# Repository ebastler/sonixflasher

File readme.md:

# sonixflasher

I made a small PCB around [the findings of silicagel777](https://github.com/silicagel777/SN8Flash) on how Sonix microcontrollers are programmed. Further information on how to use this PCB can be found in his repository.

Instead of having ot breadboard the components needed for the Sonix onewire protocol, I included those as well as a CH343 onto a single, tiny PCB with a USB-C port and ESD protection for all in/outputs.

NOTE: This PCB has not yet been tested.

|  |  |
|:---:|:---:|
| Top | Bottom |

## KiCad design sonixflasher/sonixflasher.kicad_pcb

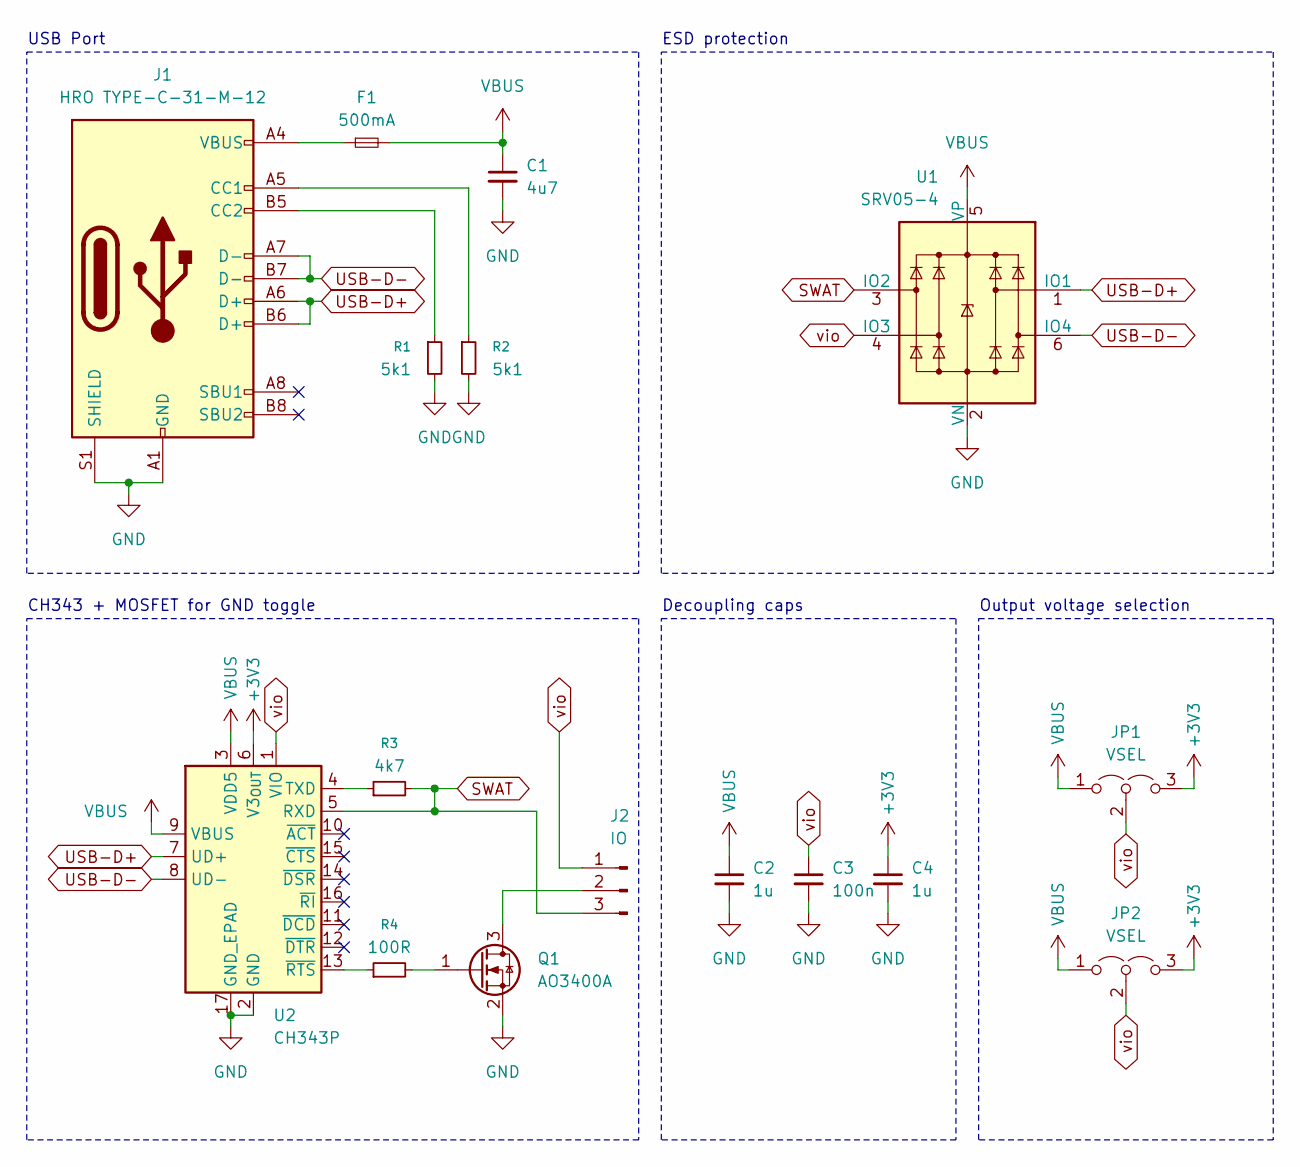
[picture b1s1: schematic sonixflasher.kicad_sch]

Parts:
C1: 4u7; C_0603_1608Metric
C2, C4: 1u; C_0402_1005Metric
C3: 100n; C_0402_1005Metric
F1: 500mA; Fuse_0603_1608Metric
J1: HRO TYPE-C-31-M-12; USB_C_Receptacle_HRO_TYPE-C-31-M-12
J2: IO; PinHeader_1x03_P2.54mm_Horizontal; LCSC C49257
JP1: VSEL; SolderJumper-3_P1.3mm_Open_RoundedPad1.0x1.5mm_NumberLabels
JP2: VSEL; PinHeader_1x03_P2.54mm_Vertical; LCSC C49257
Q1: AO3400A; SOT-23
R1, R2: 5k1; R_0402_1005Metric
R3: 4k7; R_0402_1005Metric
R4: 100R; R_0402_1005Metric
U1: SRV05-4; SOT-23-6-routable
U2: CH343P; WCH_QFN-16-1EP_3x3mm_P0.5mm_EP1.8x1.8mm

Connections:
+3V3: C4.1, JP1.3 (B), JP2.3 (B), U2.6 (V3_{OUT})
GND: C1.2, C2.2, C3.2, C4.2, J1.A1 (GND), J1.A12 (GND), J1.B1 (GND), J1.B12 (GND), J1.S1 (SHIELD), Q1.2 (S), R1.2, R2.2, U1.2 (VN), U2.2 (GND), U2.17 (GND_EPAD)
unnamed: F1.1, J1.A4 (VBUS), J1.A9 (VBUS), J1.B4 (VBUS), J1.B9 (VBUS)
unnamed: J1.A5 (CC1), R2.1
unnamed: J1.B5 (CC2), R1.1
unnamed: J2.2, Q1.3 (D)
unnamed: Q1.1 (G), R4.2
unnamed: R3.1, U2.4 (TXD)
unnamed: R4.1, U2.13 (~RTS)
SWAT: J2.3, R3.2, U1.3 (IO2), U2.5 (RXD)
USB-D+: J1.A6 (D+), J1.B6 (D+), U1.1 (IO1), U2.7 (UD+)
USB-D-: J1.A7 (D-), J1.B7 (D-), U1.6 (IO4), U2.8 (UD-)
VBUS: C1.1, C2.1, F1.2, JP1.1 (A), JP2.1 (A), U1.5 (VP), U2.3 (VDD5), U2.9 (VBUS)
vio: C3.1, J2.1, JP1.2 (C), JP2.2 (C), U1.4 (IO3), U2.1 (VIO)

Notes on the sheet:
Decoupling caps
CH343 + MOSFET for GND toggle
ESD protection
USB Port
Output voltage selection

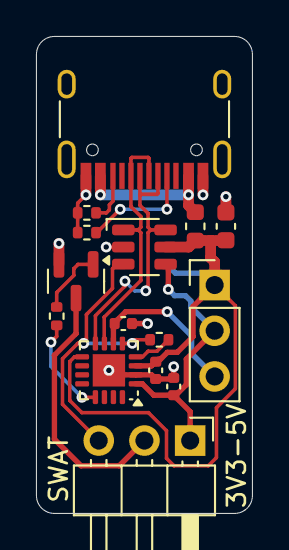
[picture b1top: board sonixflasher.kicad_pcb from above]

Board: 2 copper layers, 12.0 x 26.5 mm, 16 parts (1 on the bottom side), 14 nets.

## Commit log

2025-09-10 fix image rendering in readme
